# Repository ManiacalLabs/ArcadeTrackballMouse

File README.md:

# Arcade Trackball Mouse

A completely unnecessary, but fun computer mouse using arcade components and a billiard ball.

# Design Files

All printed parts were designed in Fusion 360 and can be viewed and downloaded here: https://a360.co/2Rxvm0l
Or find the STL files in the `Fab` folder.

# Bill of Materials

- [Happ/Atari Trackball](http://www.arcadeshop.com/i/19/2-trackball-unit-white-ball-atari-happ.htm)
- [24mm Buttons](https://www.adafruit.com/product/3432)
- [Quick Connect Button Wires](https://www.adafruit.com/product/1152)
- [#10-24 2-1/4" bolt](https://www.amazon.com/gp/product/B07B7JNY5K/)
- [#10-24 Nut](https://www.amazon.com/gp/product/B078SM2C7N/)
- [Teensy 3.2](https://www.pjrc.com/store/teensy32.html)
- [PCB @ OSHPark](https://oshpark.com/shared_projects/eHG1B3Ws) (Or see PCB folder and KiCAD files)

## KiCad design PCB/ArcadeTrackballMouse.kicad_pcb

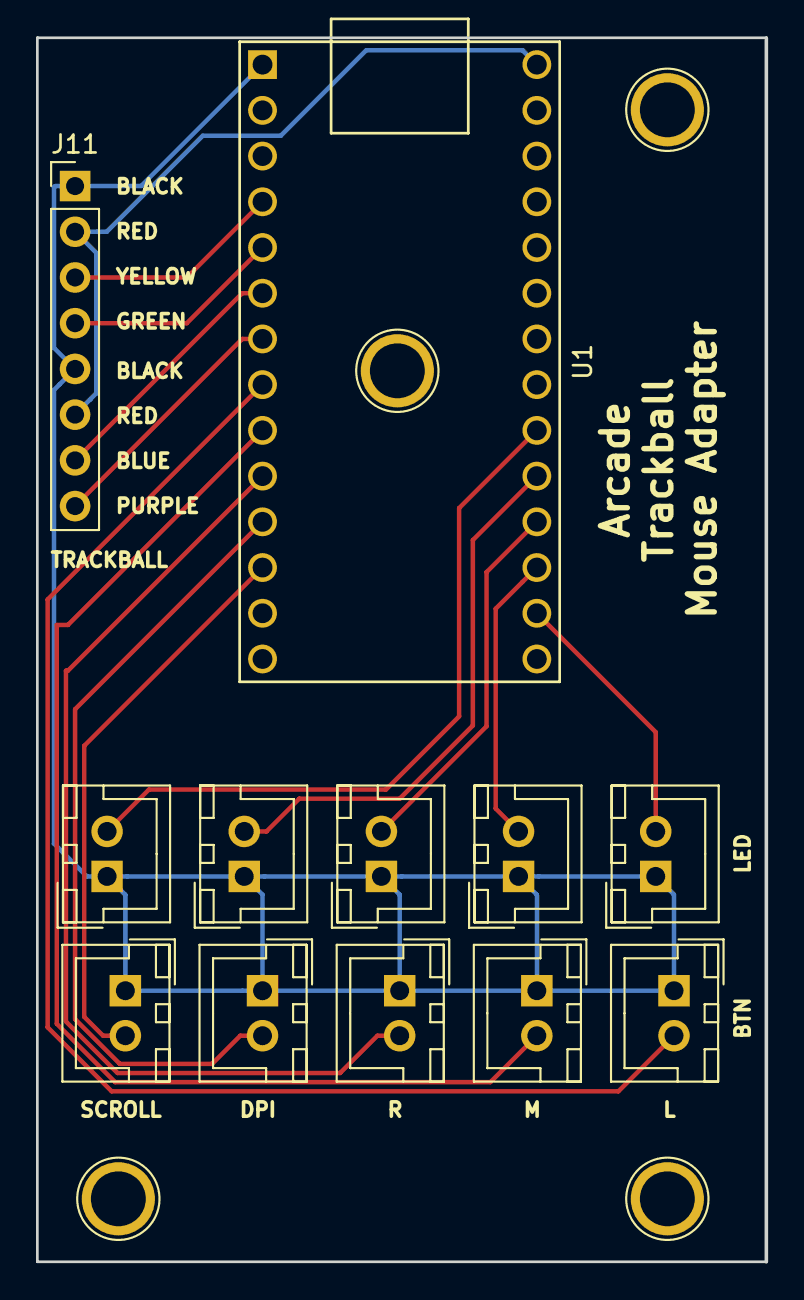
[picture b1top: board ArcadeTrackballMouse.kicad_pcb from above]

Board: 2 copper layers, 40.5 x 68.0 mm, 12 parts (0 on the bottom side), 16 nets.

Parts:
J1, J2, J3, J4, J5, J6, J7, J8, J9, J10: Conn_01x02; JST_XH_B02B-XH-A_02x2.50mm_Straight
J11: Trackball; Socket_Strip_Straight_1x08_Pitch2.54mm
U1: Teensy3.2; Teensy30_31_32_LC_NoCenterPads

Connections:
/YELLOW: J11.4, U1.5
BTN_DPI: J4.2, U1.11
BTN_L: J1.2, U1.8
BTN_M: J2.2, U1.9
BTN_R: J3.2, U1.10
BTN_SCROLL: J5.2, U1.12
GND: J1.1, J2.1, J3.1, J4.1, J5.1, J6.1, J7.1, J8.1, J9.1, J10.1, J11.1, J11.5, U1.1
LED_DPI: J9.2, U1.24
LED_L: J6.2, U1.21
LED_M: J7.2, U1.22
LED_R: J8.2, U1.23
LED_SCROLL: J10.2, U1.25
unnamed: J11.3, U1.4
unnamed: J11.7, U1.6
unnamed: J11.8, U1.7
VIN: J11.2, J11.6, U1.33

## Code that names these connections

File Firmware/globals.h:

#include "Button.h"

#define MOUSE_MULT_HIGH 4
#define MOUSE_MULT_LOW  2

#define V_A 2  // Yellow
#define V_B 3  // Green
#define H_A 4  // Blue
#define H_B 5  // Purple


#define BTNS 5 // Button Count
// Short-hand for the various arrays
#define _LEFT       0
#define _MID        1
#define _RIGHT      2
#define _SCROLL     3
#define _DPI        4

byte pattern_order[] = {_SCROLL, _DPI, _LEFT, _MID, _RIGHT};

byte btn_pins[] = {
    6,  // L
    7,  // R
    8,  // M
    10, // Scroll
    9   // DPI
};

byte led_pins[] = {
    14,  // L
    15,  // R
    16,   // M
    18,  // Scroll
    17  // DPI
};

volatile unsigned long last_int[] = {
    0,
    0,
    0,
    0,
    0
};

Button btn_scroll(btn_pins[_SCROLL]);
Button btn_dpi(btn_pins[_DPI]);
Button btn_left(btn_pins[_LEFT]);
Button btn_mid(btn_pins[_MID]);
Button btn_right(btn_pins[_RIGHT]);

Button btns[] = {
    btn_left,
    btn_mid,
    btn_right,
    btn_scroll,
    btn_dpi
};

void setup_btns(){
    for(byte i=0; i<BTNS; i++){
        btns[i].begin();
    }
}

void read_btns(){
    for(byte i=0; i<BTNS; i++){
        btns[i].read();
    }
}

void setup_leds(){
    pinMode(led_pins[_LEFT], OUTPUT);
    pinMode(led_pins[_MID], OUTPUT);
    pinMode(led_pins[_RIGHT], OUTPUT);
    pinMode(led_pins[_DPI], OUTPUT);
    pinMode(led_pins[_SCROLL], OUTPUT);

    digitalWrite(led_pins[_LEFT], LOW);
    digitalWrite(led_pins[_MID], LOW);
    digitalWrite(led_pins[_RIGHT], LOW);
    digitalWrite(led_pins[_DPI], LOW);
    digitalWrite(led_pins[_SCROLL], LOW);
}

void set_led(byte i, bool state){
    digitalWrite(led_pins[i], state);
}

#define LAST_EVENT_TIMEOUT 60000
unsigned long last_event = 0;
bool in_pattern = false;
byte pattern_dir = 1;

inline void reset_event(){last_event = millis();}

//Helper for time delays without actually pausing execution
bool TimeElapsed(unsigned long ref, unsigned long wait)
{
	static unsigned long now = 0;
	static bool result;
	result = false;
	now = millis();

	if(now < ref || ref == 0) //for the 50 day rollover or first boot
		result = true;
	else if((now - ref) > wait)
		result = true;

	return result;
}

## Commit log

2018-10-10 POC firmware working
2018-11-15 Adding PCB
2019-01-12 backup
2019-01-12 Backup ISR work
2019-01-12 Initial working state
2019-01-13 Final version
2019-01-22 Add STL Files
2019-01-22 adding F360 files
